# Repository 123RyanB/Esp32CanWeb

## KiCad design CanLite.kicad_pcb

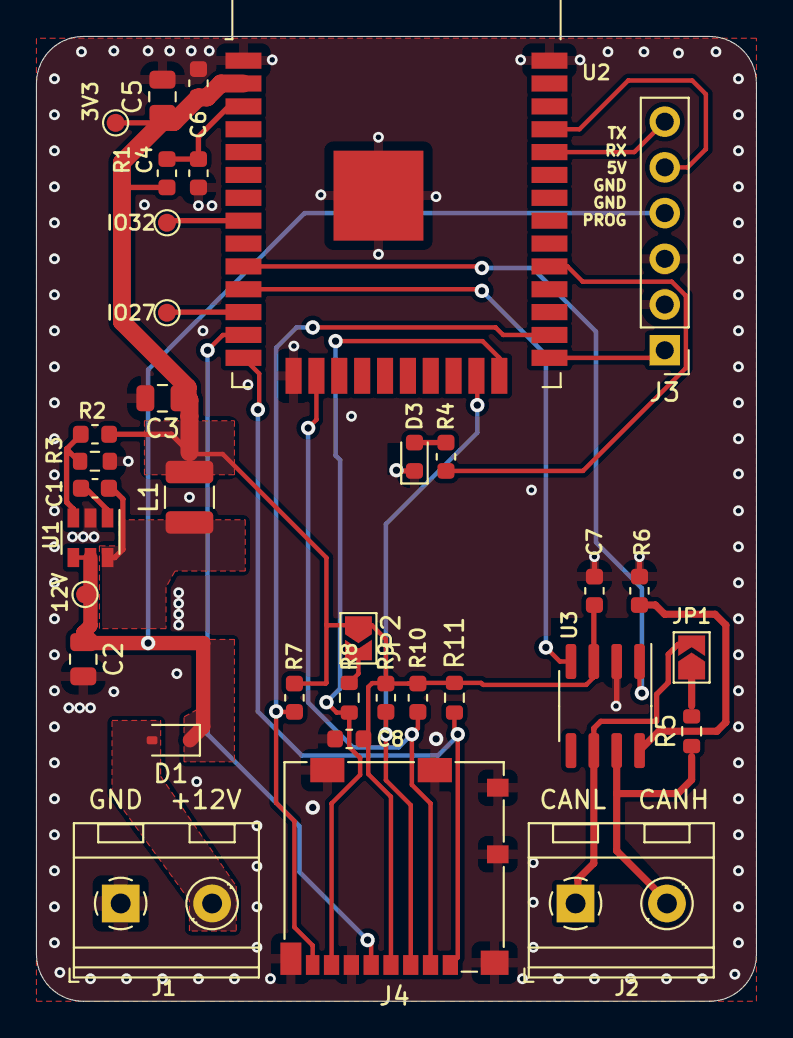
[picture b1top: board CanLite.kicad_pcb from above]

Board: 2 copper layers, 40.0 x 53.6 mm, 35 parts (0 on the bottom side), 28 nets.

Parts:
C1, C4, C6, C7, C8: 0.1uF; C_0603_1608Metric
C2, C3: 10uF; C_0805_2012Metric
C5: 22uF; C_0805_2012Metric
D1: 1N4148; D_SOD-323
D3: LED; LED_0603_1608Metric
J1: 12V; TerminalBlock_RND_205-00232_1x02_P5.08mm_Horizontal
J2: CAN; TerminalBlock_RND_205-00232_1x02_P5.08mm_Horizontal
J3: PinHeader_1x06_P2.54mm_Vertical
J4: Molex_104031-0811; microSD_HC_Molex_104031-0811
JP1, JP2: NO; SolderJumper-2_P1.3mm_Open_TrianglePad1.0x1.5mm
L1: 4.7uH; L_1210_3225Metric
R1, R3, R7, R8, R9, R10: 10k; R_0603_1608Metric
R2: 28K; R_0603_1608Metric
R4: 1K; R_0603_1608Metric
R5: 120; R_0603_1608Metric
R6: 10K; R_0603_1608Metric
R11: na; R_0603_1608Metric
TP1: VIN; TestPoint_Pad_D1.0mm
TP2: 3V3; TestPoint_Pad_D1.0mm
TP5: IO27; TestPoint_Pad_D1.0mm
TP6: IO32; TestPoint_Pad_D1.0mm
U1: SCT2401; SOT-23-6
U2: ESP32-WROOM-32D; ESP32-WROOM-32
U3: SN65HVD231; SOIC-8_3.9x4.9mm_P1.27mm

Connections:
+3V3: C3.1, C5.1, C6.1, C7.1, C8.1, J4.4 (VDD), JP2.1 (A), L1.2, R1.1, R2.1, R7.2, R9.2, R10.2, R11.2, TP2.1, U2.2 (VDD), U3.3 (VCC)
+12V: D1.2 (A), J1.2
/12V_INT: C2.1, D1.1 (K), J3.4, TP1.1, U1.4 (~SHDN), U1.5 (VIN)
/CAN0_RX: U2.11 (IO26), U3.4 (R)
/CAN0_TX: U2.10 (IO25), U3.1 (D)
/CAN_H: J2.2, R5.1, U3.7 (CANH)
/CAN_L: J2.1, JP1.2 (B), U3.6 (CANL)
/EN: C4.1, R1.2, U2.3 (EN)
/IO0: J3.1, U2.25 (IO0)
/IO2: J4.7 (DAT0), R8.1, U2.24 (IO2)
/IO4: J4.8 (DAT1), R7.1, U2.26 (IO4)
/IO12: J4.1 (DAT2), R11.1, U2.14 (IO12)
/IO13: J4.2 (DAT3/CD), R10.1, U2.16 (IO13)
/IO14: J4.5 (CLK), U2.13 (IO14)
/IO15: J4.3 (CMD), R9.1, U2.23 (IO15)
/IO27: TP5.1, U2.12 (IO27)
/IO32: TP6.1, U2.8 (IO32)
/RXD: J3.6, U2.34 (RXD0/IO3)
/TXD: J3.5, U2.35 (TXD0/IO1)
GND: C2.2, C3.2, C4.2, C5.2, C6.2, C7.2, C8.2, D3.1 (K), J1.1, J3.2, J3.3, J4.6 (VSS), J4.9 (DET_B), J4.10 (DET_A), J4.11 (SHIELD), R3.2, R6.2, U1.2 (GND), U2.1 (GND), U2.15 (GND), U2.38 (GND), U2.39 (GND), U3.2 (GND)
unnamed: D3.2 (A), R4.1
unnamed: JP1.1 (A), R5.2
unnamed: JP2.2 (B), R8.2
unnamed: C1.1, U1.1 (CB)
unnamed: R2.2, R3.1, U1.3 (FB)
unnamed: C1.2, L1.1, U1.6 (SW)
unnamed: R4.2, U2.29 (IO5)
unnamed: R6.1, U3.8 (Rs)

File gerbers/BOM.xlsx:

Comment | Designator | Footprint | LCSC Part #
0.1uF | C1, C4, C6, C7, C8 | Capacitor_SMD:C_0603_1608Metric | C14663
10uF | C2, C3 | Capacitor_SMD:C_1206_3216Metric | C15850
22uF | C5 | Capacitor_SMD:C_1206_3216Metric | C45783
1N4148 | D1 | Diode_SMD:D_SOD-128 | C2128
LED | D3 | LED_SMD:LED_0603_1608Metric | C84256
Molex_104031-0811 | J4 | Connector_Card:microSD_HC_Molex_104031-0811 | C585350
4.7uH | L1 | Inductor_SMD:L_Bourns_SRU5016_5.2x5.2mm | C90319
10k | R1, R3, R6, R7, R8, R9, R10 | Resistor_SMD:R_0603_1608Metric | C25804
28K | R2 | Resistor_SMD:R_0603_1608Metric | C22984
1K | R4 | Resistor_SMD:R_0603_1608Metric | C21190
120 | R5 | Resistor_SMD:R_0603_1608Metric | C22787
SCT2401 | U1 | Package_TO_SOT_SMD:SOT-23-6 | C2830166
ESP32-WROOM-32D | U2 | RF_Module:ESP32-WROOM-32 | C82899
SN65HVD231 | U3 | Package_SO:SOIC-8_3.9x4.9mm_P1.27mm | C12084

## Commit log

2024-07-21 Removed high side drivers, added SD card reader
2024-07-21 Added new schematic and image
2024-10-12 Silkscreen edit
    Corrected pin labels on programming header
2024-10-12 Delete gerbers/CanLite-F_SilkS.gbr
    from original, conflicts with the correct file when uploaded to JLCPCB
2024-10-12 Delete gerbers/CanLite-B_SilkS.gbr
    from original, conflicts with the correct file when uploaded to JLCPCB
